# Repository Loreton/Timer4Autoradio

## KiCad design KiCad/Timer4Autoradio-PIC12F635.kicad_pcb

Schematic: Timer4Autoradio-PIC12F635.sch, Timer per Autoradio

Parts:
C1, C3: 100nF
C2, C4: 10uF
D1: 1N4001
D2: 1N4148
DL1, DL2: LED
IC1: 4N35
J1: 12Vcc
J2: ExtLED
J3: CONN_05
PB1: PButton
Q1: BC337-BC238
R1, R4: 25K
R2: 4K7
R3: 2K2
R5: 330
R6: 470
R7: 2k2
RL1: RELAY_AUTORADIO
U1: 78L05
U2: PIC12F635_4

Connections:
+5V: C2.+, C3.1, J3.2, R4.1, U1.VO, U2.1 (VDD)
+12V: D1.1 (A), J1.1
/+12V_CMD: J1.2, R1.1, R2.1
/+12Vcc (Autoradio): C1.1, J1.3, RL1.2, U1.VI
/ClockOUT: R5.1, U2.3 (GP4/CLKOUT)
GND: C1.2, C2.-, C3.2, DL2.2 (K), IC1.2, IC1.4, J1.4, J2.2, J3.3, PB1.2, Q1.E, R3.2, R7.2, U1.GND, U2.8 (VSS)
ICSPCLK: J3.5, U2.6 (GP1/C1IN-/CLK)
ICSPDAT: J3.4, R2.2, R3.1, U2.7 (GP0/C1IN+/DAT)
unnamed: R6.2, U2.2 (GP5/CLKIN)
unnamed: DL1.1 (A), R5.2
unnamed: DL1.2 (K), IC1.1
unnamed: DL2.1 (A), J2.1, R6.1
unnamed: PB1.1, U2.5 (GP2/INT/COUT)
unnamed: C4.-, Q1.B, R7.1
unnamed: D2.1 (A), IC1.5, Q1.C, RL1.13
unnamed: C4.+, R1.2
unnamed: D1.2 (K), D2.2 (K), RL1.9, RL1.14
VPP/MCLR: J3.1, R4.2, U2.4 (GP3/MCLR)

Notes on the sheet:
3.98 Volt
circa 5mA

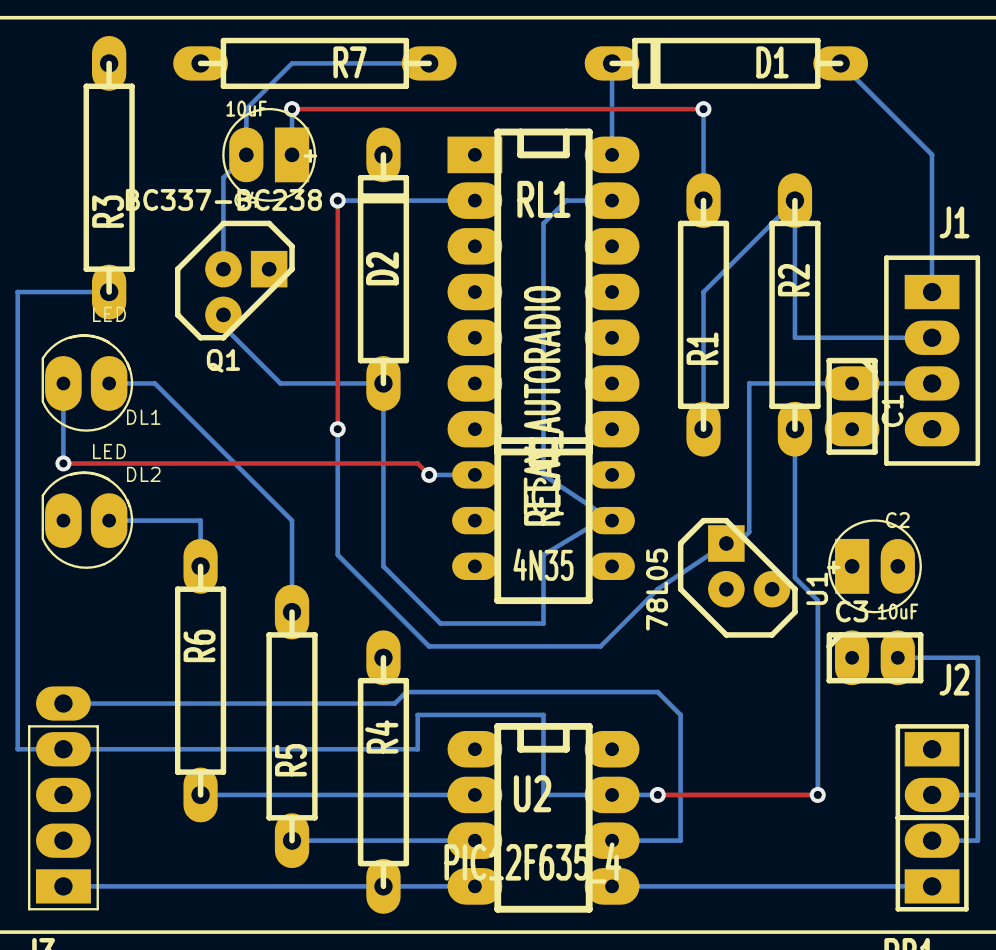
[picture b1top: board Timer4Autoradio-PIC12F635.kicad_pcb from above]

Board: 6 copper layers, 24 parts (0 on the bottom side), 18 nets.

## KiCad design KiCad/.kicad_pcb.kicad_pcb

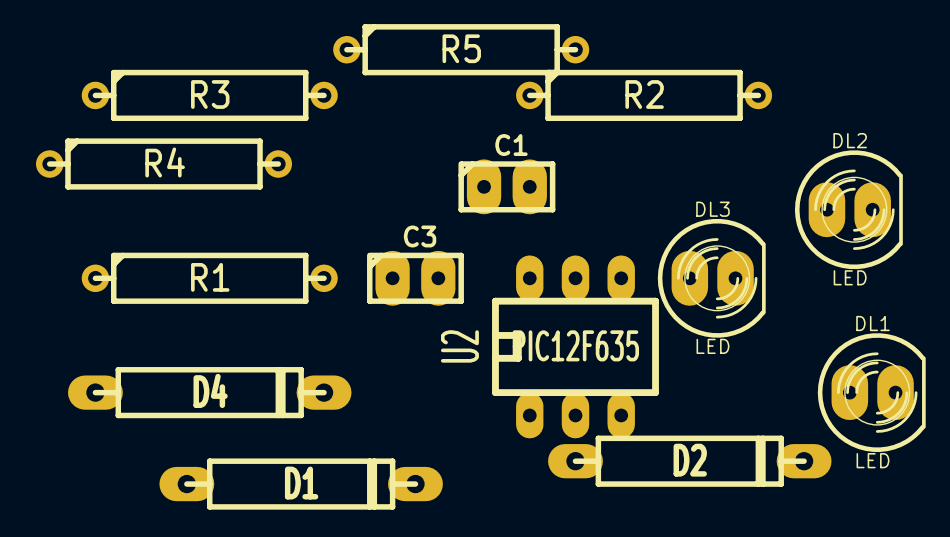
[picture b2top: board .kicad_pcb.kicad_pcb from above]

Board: 2 copper layers, 14 parts (0 on the bottom side), 8 nets, no tracks yet.

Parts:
C1, C3: C; Cap_100
D1: 1N4001; Diode_500
D2: 1N4148; Diode_500
D4: DIODE; Diode_500
DL1, DL2, DL3: LED; LED-5MM
R1: 27K; R5
R2: 100K; R5
R3: 25K; R5
R4: 470; R5
R5: 470K; R5
U2: PIC12F635; Ln_DIP-6_300

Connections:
+5V: R3.1, U2.1
/Out: R4.2, U2.3
GND: C1.2, C3.2, DL3.2, R2.2
unnamed: DL2.1, R4.1
unnamed: R1.2, R2.1
unnamed: R5.2, U2.2
unnamed: DL3.1, R5.1
VPP/MCLR: R3.2, U2.4

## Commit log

2015-02-05 2015-02-05 10:44 - commit with no comment
2015-02-06 2015-02-06 07:49 - commit with no comment
2015-02-10 Versione consolidata con il PIC
2017-02-28 2017-02-28 08:04 - commit with no comment
